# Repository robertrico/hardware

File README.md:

# Embedded Systems Portfolio

Welcome to my Embedded Systems Portfolio. This document introduces several projects, highlighting their objectives, technologies, and current status.

---

## LED Blinky Projects

#### Zephyr RTOS Blinky on Raspberry Pi Pico

* **Objective**: GPIO control demonstration using Zephyr RTOS.
* **Technologies**: Raspberry Pi Pico, Zephyr RTOS, DeviceTree.
* **Current Status**: Complete.

#### FreeRTOS LED Blinky for Pico W, Pico W2, ESP32

* **Objective**: Basic FreeRTOS demonstration with task scheduling and GPIO control.
* **Technologies**: FreeRTOS, Raspberry Pi Pico W, Pico W2, ESP32.
* **Current Status**: Complete

## PicoBook

* **Objective**: A compact device fetching and displaying book data via Wi-Fi.
* **Technologies**: Raspberry Pi Pico W, MicroPython, OLED display, Wi-Fi.
* **Current Status**: Complete.

## Zephyr OS "Hello World" on Raspberry Pi Pico

* **Objective**: Minimal Zephyr OS application printing to USB serial.
* **Technologies**: Zephyr OS, RP2040.
* **Current Status**: Complete

## PicoW Over-The-Air (OTA) Firmware System

* **Objective**: Dual-partition bootloader enabling OTA firmware updates.
* **Technologies**: RP2040, pico-sdk, assembly, linker scripts.
* **Current Status**: Complete - But inoperable. There were struggles with the bootloader and ROM and highlighted knowledge gaps. This work was the catalyst for a full re-understanding of low level work. Inspiring the DINO project.

## ESP-NOW Remote Control Project

* **Objective**: Wireless remote control for toggling LEDs using ESP-NOW protocol.
* **Technologies**: ESP32-C3, ESP-IDF, ESP-NOW.
* **Current Status**: Complete

## The Earth Rover

* **Objective**: Modular rover system using ESP-NOW and STM32 for real-time motor control and wireless ADC data transmission.
* **Technologies**: ESP32-C3, STM32L432KC, ESP-NOW, FreeRTOS, STM32CubeMX, CMake, SPI, DMA, TB6612FNG, CD4053BE.
* **Current Status**: Communication functional; currently refining SPI packetization and synchronization.

## Dino (Discrete Integrated NISC Operator) CPU

#### Dino v0.01 – Manual Logic Sequencer

* **Objective**: CPU-free logic sequencer manually steps through memory and outputs 8-bit values via LEDs.
* **Technologies**: SN74LS590N counters, 555 timer, SRAM, DIP switches, LEDs.
* **Current Status**: In Progress. Schematic Phase.

#### Dino v0.1 – 8-bit CPU Core

* **Objective**: Upgrade to a functional 8-bit CPU with ALU, registers, and basic arithmetic operations.
* **Technologies**: 74F382N ALU, SN74LS273N registers, DM74LS374 latch.
* **Current Status**: Planned

#### Dino v0.1.1 – Instruction Decoder & 7-Segment Display

* **Objective**: Adds instruction decoding and output display.
* **Technologies**: SN74LS138N decoder, 7-segment display drivers.
* **Current Status**: Planned

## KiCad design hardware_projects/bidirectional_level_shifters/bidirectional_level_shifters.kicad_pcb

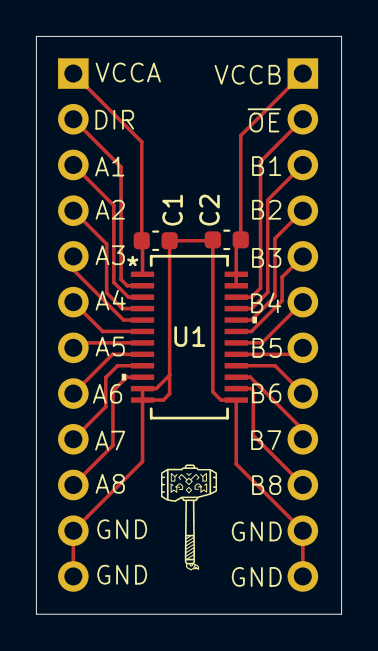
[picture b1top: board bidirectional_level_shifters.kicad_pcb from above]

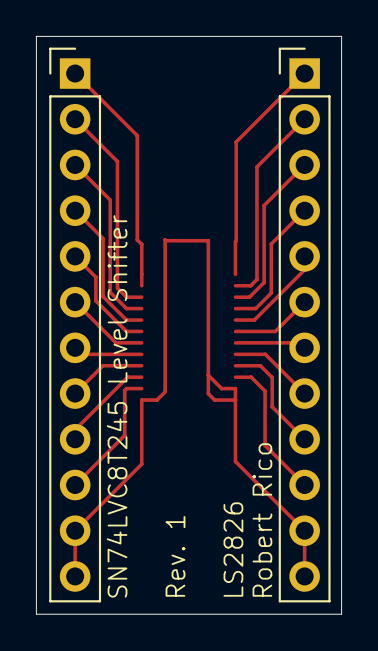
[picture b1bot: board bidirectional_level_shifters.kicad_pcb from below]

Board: 2 copper layers, 17.0 x 32.1 mm, 5 parts (2 on the bottom side), 21 nets.

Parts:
C1, C2: C_Small; C_0603_1608Metric
J1, J2: Conn_01x12_Socket; PinHeader_1x12_P2.54mm_Vertical
U1: SN74LVC8T245; DBQ24-L

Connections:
A1: J1.3, U1.3 (A1)
A2: J1.4, U1.4 (A2)
A3: J1.5, U1.5 (A3)
A4: J1.6, U1.6 (A4)
A5: J1.7, U1.7 (A5)
A6: J1.8, U1.8 (A6)
A7: J1.9, U1.9 (A7)
A8: J1.10, U1.10 (A8)
B1: J2.3, U1.21 (B1)
B2: J2.4, U1.20 (B2)
B3: J2.5, U1.19 (B3)
B4: J2.6, U1.18 (B4)
B5: J2.7, U1.17 (B5)
B6: J2.8, U1.16 (B6)
B7: J2.9, U1.15 (B7)
B8: J2.10, U1.14 (B8)
DIR: J1.2, U1.2 (DIR)
GND: C1.2, C2.2, J1.11, J1.12, J2.11, J2.12, U1.11 (GND), U1.12 (GND), U1.13 (GND)
VCCA: C1.1, J1.1, U1.1 (V_{CCA})
VCCB: C2.1, J2.1, U1.23 (V_{CCB}), U1.24 (V_{CCB})
~OE: J2.2, U1.22 (~OE)

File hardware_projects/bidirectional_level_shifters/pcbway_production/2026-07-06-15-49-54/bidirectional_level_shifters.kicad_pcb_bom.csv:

Designator,Quantity,Value,Mfg Part #,Description / Value,Package/Footprint,Type,Notes
"C1, C2",2,0.1uF,CC0603KRX7R9BB104,Multilayer Ceramic Capacitors MLCC - SMD/SMT 50 V 0.1uF X7R 0603 10%,0603 (1608 metric),smt,"Unpolarized capacitor, small symbol"
"J1, J2",2,Conn_01x12_Socket,,,,tht,Excluded from BOM
U1,1,SN74LVC8T245,SN74LVC8T245DBQR,Translation - Voltage Levels 8-Bit Dual-Supply Bu s Xcvr,DBQ24-L / QSOP-24,smt,8-Bit Dual-Supply Bus Transceiver With Configurable Voltage Translation and 3-State Outputs

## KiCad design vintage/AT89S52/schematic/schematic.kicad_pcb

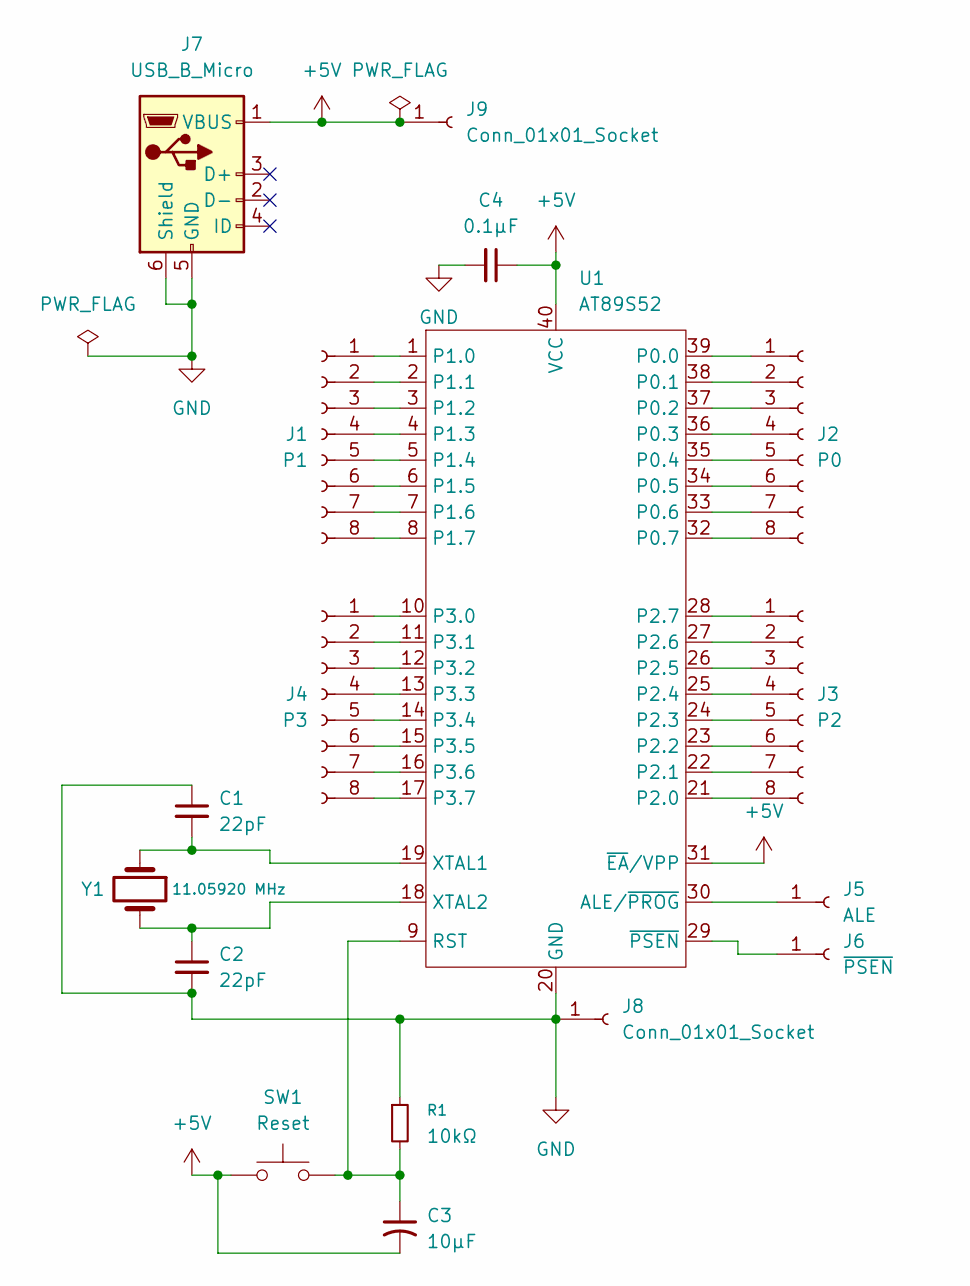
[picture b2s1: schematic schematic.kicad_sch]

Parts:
C1, C2: 22pF; C_Disc_D3.0mm_W1.6mm_P2.50mm
C3: 10µF; CP_Radial_D4.0mm_P2.00mm
C4: 0.1µF; C_Disc_D5.0mm_W2.5mm_P5.00mm
J1: P1; PinHeader_1x08_P2.54mm_Vertical
J2: P0; PinHeader_1x08_P2.54mm_Vertical
J3: P2; PinHeader_1x08_P2.54mm_Vertical
J4: P3; PinHeader_1x08_P2.54mm_Vertical
J5: ALE; PinHeader_1x01_P2.54mm_Vertical
J6: ~{PSEN}; PinHeader_1x01_P2.54mm_Vertical
J7: USB_B_Micro; USB_A_Connfly_DS1095
J8, J9: Conn_01x01_Socket; PinHeader_1x01_P2.54mm_Vertical
R1: 10kΩ; R_Axial_DIN0309_L9.0mm_D3.2mm_P12.70mm_Horizontal
SW1: Reset; SW_PUSH_6mm
U1: AT89S52; DIP_Socket-40_W11.9mm_W12.7mm_W15.24mm_W17.78mm_W18.5mm_3M_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
Y1: 11.05920 MHz; Crystal_HC49-U_Horizontal

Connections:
+5V: C3.2, C4.1, J7.1 (VBUS), J9.1, SW1.1, U1.31 (~EA/VPP), U1.40 (VCC)
GND: C1.1, C2.2, C4.2, J7.5 (GND), J7.6 (Shield), J8.1, R1.1, U1.20 (GND)
unnamed: J1.1, U1.1 (P1.0)
unnamed: J1.2, U1.2 (P1.1)
unnamed: J1.3, U1.3 (P1.2)
unnamed: J1.4, U1.4 (P1.3)
unnamed: J1.5, U1.5 (P1.4)
unnamed: J1.6, U1.6 (P1.5)
unnamed: J1.7, U1.7 (P1.6)
unnamed: J1.8, U1.8 (P1.7)
unnamed: J2.1, U1.39 (P0.0)
unnamed: J2.2, U1.38 (P0.1)
unnamed: J2.3, U1.37 (P0.2)
unnamed: J2.4, U1.36 (P0.3)
unnamed: J2.5, U1.35 (P0.4)
unnamed: J2.6, U1.34 (P0.5)
unnamed: J2.7, U1.33 (P0.6)
unnamed: J2.8, U1.32 (P0.7)
unnamed: J3.1, U1.28 (P2.7)
unnamed: J3.2, U1.27 (P2.6)
unnamed: J3.3, U1.26 (P2.5)
unnamed: J3.4, U1.25 (P2.4)
unnamed: J3.5, U1.24 (P2.3)
unnamed: J3.6, U1.23 (P2.2)
unnamed: J3.7, U1.22 (P2.1)
unnamed: J3.8, U1.21 (P2.0)
unnamed: J4.1, U1.10 (P3.0)
unnamed: J4.2, U1.11 (P3.1)
unnamed: J4.3, U1.12 (P3.2)
unnamed: J4.4, U1.13 (P3.3)
unnamed: J4.5, U1.14 (P3.4)
unnamed: J4.6, U1.15 (P3.5)
unnamed: J4.7, U1.16 (P3.6)
unnamed: J4.8, U1.17 (P3.7)
unnamed: J5.1, U1.30 (ALE/~PROG)
unnamed: J6.1, U1.29 (~PSEN)
unnamed: C3.1, R1.2, SW1.2, U1.9 (RST)
unnamed: C1.2, U1.19 (XTAL1), Y1.1
unnamed: C2.1, U1.18 (XTAL2), Y1.2

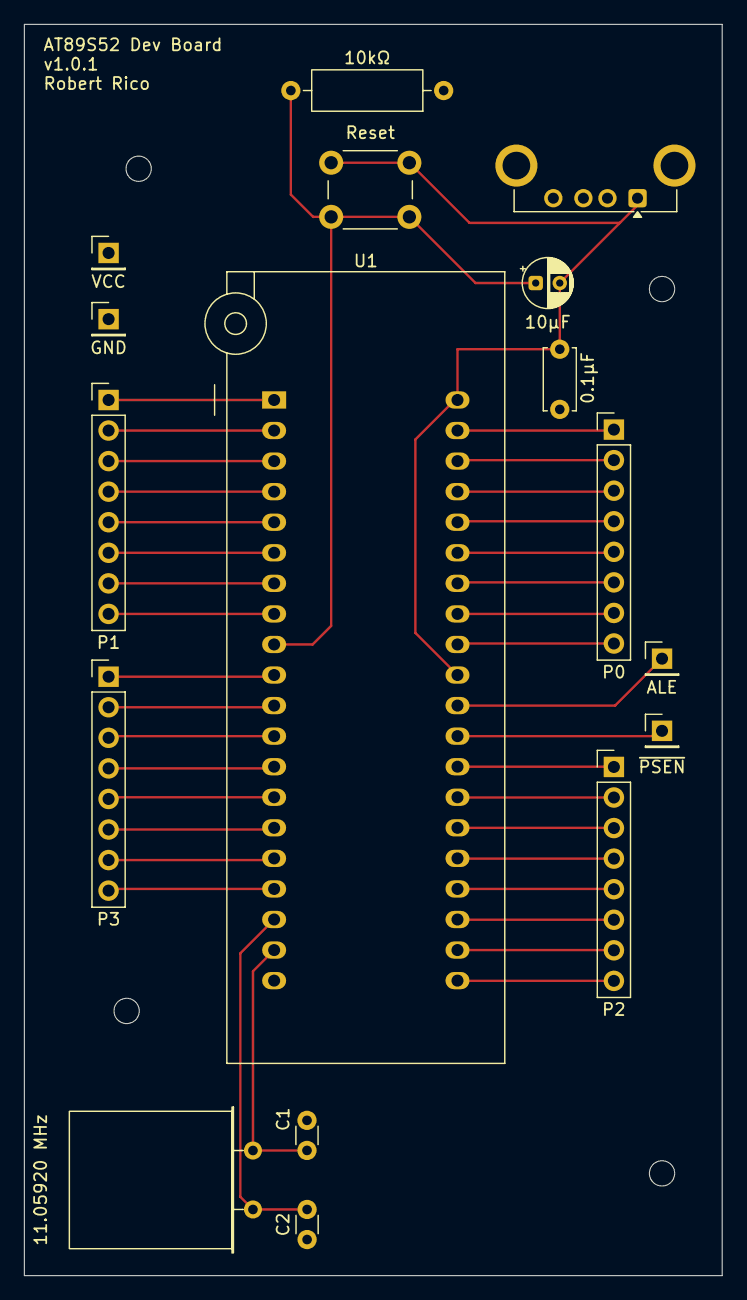
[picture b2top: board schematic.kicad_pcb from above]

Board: 2 copper layers, 58.0 x 104.0 mm, 17 parts (0 on the bottom side), 39 nets.

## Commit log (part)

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2025-03-29 Initial Test Projects
    - Created CMakeLists.txt for the Wi-Fi test project
    - Set up Pico SDK and board configuration
    - Added executable target with main.c
    - Included necessary libraries for I2C and SSD1306 support
    - Linked additional libraries for Wi-Fi functionality
    - Introduced font header files for text rendering
2025-04-14 Add server script and update main functionality
    - Created a new script for SSH access.
    - Changed button pin from 16 to 0.
    - Improved text wrapping logic for OLED display.
    - Centered text on the OLED screen.
    - Added exception handling for clean exit on button press.
    - Updated README with new commands for file upload and REPL connection.
2025-04-14 Updates landing page and project structure
    Modernizes the landing page with a project listing,
    skills section, and introduction.
    Restructures the project to include a dedicated skills
    directory and a more descriptive project overview.
    Removes the minima theme and cleans up the configuration.
2025-04-18 Adds boot flag functionality for OTA updates
    Implements the ability to write and check a boot flag in flash memory, enabling the system to switch to the newly updated firmware in the B partition after an OTA update.
    Also changes version string in version.h to use underscores instead of periods.
2025-04-26 Refactors Wi-Fi connection initialization
    Moves Wi-Fi initialization and connection logic to static methods within the WiFiManager class.
    This change simplifies the bootloader code by centralizing Wi-Fi management and ensures proper initialization before attempting a connection.
2025-04-27 Enhances firmware build optimization
    Introduces a shared function to streamline compile and link options,
    emphasizing size optimization flags. Updates linker script to allocate
    BOOT_CONFIG memory and adjusts stack usage limit to improve memory
    efficiency.
    Removes redundant flash mapping definitions to simplify memory map.
2025-05-03 Initialize PWM motor control project
    Sets up a new project for controlling a motor via PWM using the Raspberry Pi Pico. Adds necessary CMake files for building the project with the Pico SDK and includes logic for GPIO configuration and 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
    No related issue or ticket specified.
2025-05-19 Project Clean Up. 1 - 9
2025-05-23 Refactors code to modularize interrupts and config
    Moves interrupt handling logic from main to a dedicated module for better separation of concerns.
    Extracts configuration macros and utility headers to a central include directory.
    Renames and reorganizes component files for clarity and maintainability.
    Improves code organization to facilitate future feature development.
2025-05-29 Adds DMA support for SPI1 with interrupt and RX channel
    Enables DMA peripheral for SPI1 by introducing DMA initialization,
    configuring DMA1 Channel 2 for SPI1_RX, and handling its interrupts.
    Updates peripheral setup to initialize DMA before SPI.
    Integrates DMA handler with SPI1 to offload data transfers and
    improve performance.
    Facilitates more efficient SPI communication.
2025-06-09 Add Schematics
2025-06-16 Removes backup files and updates .gitignore
    Deletes several backup ZIP files from the repository.
    Adds a new pattern to .gitignore to prevent future
    backup files from being tracked.
    Enhances project cleanliness by avoiding unnecessary
    backup files in version control.
2025-06-19 Adds deadband to reduce unnecessary SPI and ESP-NOW traffic
    Implements a deadband filter to prevent sending data when ADC values are within a neutral range, minimizing redundant communications between transmitter and receiver and reducing system noise and res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
2025-06-21 Reorganizes project documentation structure
    Moves several project-related documents into a unified 'project_notes' directory
    Enhances accessibility and organization of project documentation
    Adds Rover project notes
2025-06-24 Configures GPIO for chip select output
    Adds dedicated GPIO setup for chip select line, improving
    SPI communication reliability by ensuring proper initialization
    of the chip select pin.
2025-06-30 Adds datasheet, documentation, and test files
    Introduces relevant hardware datasheets and new documentation files to support project development. Includes a new test case for further validation and several temp files likely associated with activ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
2025-07-04 Adds SRAM datasheet and test DSL files
    Introduces the SRAM datasheet for reference and includes new DSL-based test files to support rewire and high/low PC scenarios. Enhances test coverage and hardware documentation.
2025-07-10 Simplifies README content for ESP-NOW example
    Removes detailed setup and logic explanations from both receiver
    and transmitter READMEs to streamline documentation. Focuses on
    essential setup steps, reducing redundancy and improving clarity.
2025-07-20 Adds new documentation screenshot
    Introduces an updated screenshot to enhance the documentation's visual references and clarity for users.
2025-07-26 Adds ring counter 16-state test case
    Introduces a new test to verify 16-state ring counter functionality,
    enabling more comprehensive validation of state transitions and behavior.
2025-08-08 Schematics WIP
2025-08-17 PDF Update
2025-08-24 Add instruction register (244+373) test and docs
    - Adds a comprehensive test for the instruction register module using 74LS244 and 74LS373 chips, including reset override behavior
    - Integrates instruction register test into build system and main entry point
    - Documents IR test wiring, usage, and LED indications in TESTS.md
    - Provides a detailed wiring troubleshooting checklist for the 245+373 test
    Expands test suite for more robust hardware validation.
2025-08-24 Add hardware register module test with 121 pulse support
    - Introduces comprehensive testing for a register module using 74LS373, 74LS245, and 74LS121 hardware
    - Supports automated latch pulsing via monostable multivibrator
    - Updates build system and main logic for easy selection and execution
    Ensures reliable, hardware-timed register testing for accurate validation.
2025-08-30 Improves register timing test clarity and bus writes
    - Ensures atomic bus writes by preparing port values before output
    - Refactors control word updates for cleaner transitions
    - Clarifies hardware direction and test procedure comments
    - Adds logic analyzer output signaling and removes floating pin check
    - Includes detailed design issue exploration and documentation for register timing failure
2025-09-02 Refactors receiver for direct motor control
    - Replaces SPI-based motor commands with integrated direct PWM motor control
    - Introduces modular arcade drive, motor controller, and TB6612FNG driver components
    - Updates build configuration to remove SPI dependencies and add new modules
    - Cleans up legacy motor and SPI code from receiver
    - Adjusts include files and project structure for new architecture
    - Updates serial port configuration for both receiver and transmitter
2025-09-17 Adds 3D models for rover components
    Includes new files for the physical design components of the
    earth rover project. Introduces key models such as Body,
    Buck Converter Mount, and TX Mount to support hardware upgrades
    and assembly visualization.
2025-10-12 Increases throttle speed limit for precise operations
    Raises the allowed throttle from 40% to 75% during precise
    scientific tasks to improve maneuverability and speed.
    Updates the serial port configuration for device connection.
2025-10-15 Refactors test build system for multi-test support
    - Renames files and updates CMake config to support multiple AVR Mega 2560 test targets
    - Simplifies and generalizes flash script for selecting and flashing individual tests
    - Replaces single-test setup with flexible test registration and flashing mechanism
    - Streamlines build, flash, and clean operations for future test scalability
2025-10-20 Adds modernization changes for AS9 assembler
    Introduces documentation detailing modifications for porting the AS9 assembler to Linux and Apple Silicon, including a shift to modern C standards.
    Adds relevant documentation files and organizes project structure to support Motorola 6809 development on contemporary systems.
    Enhances compatibility with modern compilers by updating function prototypes and removing obsolete declarations.
    Enables building ROM images on Apple Silicon and verifies functionality with test assembly programs. These changes maintain original assembler functionality while ensuring compatibility with current 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
2025-10-22 Streamlines FPGA project setup and tooling
    Consolidates .gitignore entries by merging two files into the root
    .gitignore for more efficient management of ignored files related
    to FPGA development.
    Removes the toolchain verification script and associated Makefile
    target and README instructions, simplifying project setup by assuming
    tools are pre-installed or managed outside the repo.
2025-10-24 Refactors FPGA ignore rules into separate file
    Moves FPGA-specific ignore patterns from the main .gitignore to
    a dedicated .gitignore in the FPGA directory for improved clarity
    and maintainability. This separation helps manage neglect of
    FPGA artifacts and environment files more effectively, while
    keeping the global .gitignore cleaner.
2025-10-26 Adds serial loading feature for ASSIST09
    Introduces a 'load' target to Makefile for loading S19 files to
    ASSIST09 via a specified serial port. Provides error handling and
    user prompts to ensure correct operation. Updates help documentation
    to reflect new functionality.
    Users can now load compiled programs to ASSIST09 more easily,
    enhancing the development workflow for projects using this
2025-10-29 Adds IC Datasheets
2025-10-30 Add attribution and licensing documentation
    Introduces detailed attribution, licensing, and acknowledgment
    documentation for the VHDL implementation of the Intel SIM8-01
    reference design, highlighting the adaptation from Michael Kohn's
    Verilog work and the original contributions by Robert Rico.
    Provides a disclaimer for educational and historical preservation
    purposes, and outlines the terms of the MIT License.
2025-11-01 Move ISS Implementation to subfolders
    Original implementation was an emulated instruction set simulator. Want a more hardware implementation.
2025-11-02 Introduces debug toggle for clock phase reporting
    Adds a DEBUG_VERBOSE constant to control the verbosity of
    clock phase toggle messages during simulation. This reduces
    output noise when unnecessary log details are not needed.
    Improves simulation efficiency by allowing targeted debugging.
2025-11-03 Adds assembly and loading features to Makefile
    Introduces program assembly and ROM loading functionalities,
    enabling the assembly of specified test programs and their
    integration into the ROM. Updates test configurations with
    new test stops and enhances ROM component for loading
    different files.
    Improves workflow efficiency and testing flexibility.
2025-11-03 Removes unused I/O ports from testbenches
    Eliminates redundant I/O port signals and associated logic
    in several VHDL testbench files to streamline code and
    improve maintainability. Updates the s8008 main component
    to employ an internal hand-off mechanism for I/O port
    operations, removing direct port handling logic from the
    testbenches. This change facilitates a more modular and
2025-11-13 Updates Arduino Code
